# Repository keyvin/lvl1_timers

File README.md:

Maintenance interval timers for lvl1. 

Edit the defaults in micropython/lvl1_timers.py. Use Thonny to upload to micropython

reporting server a WIP

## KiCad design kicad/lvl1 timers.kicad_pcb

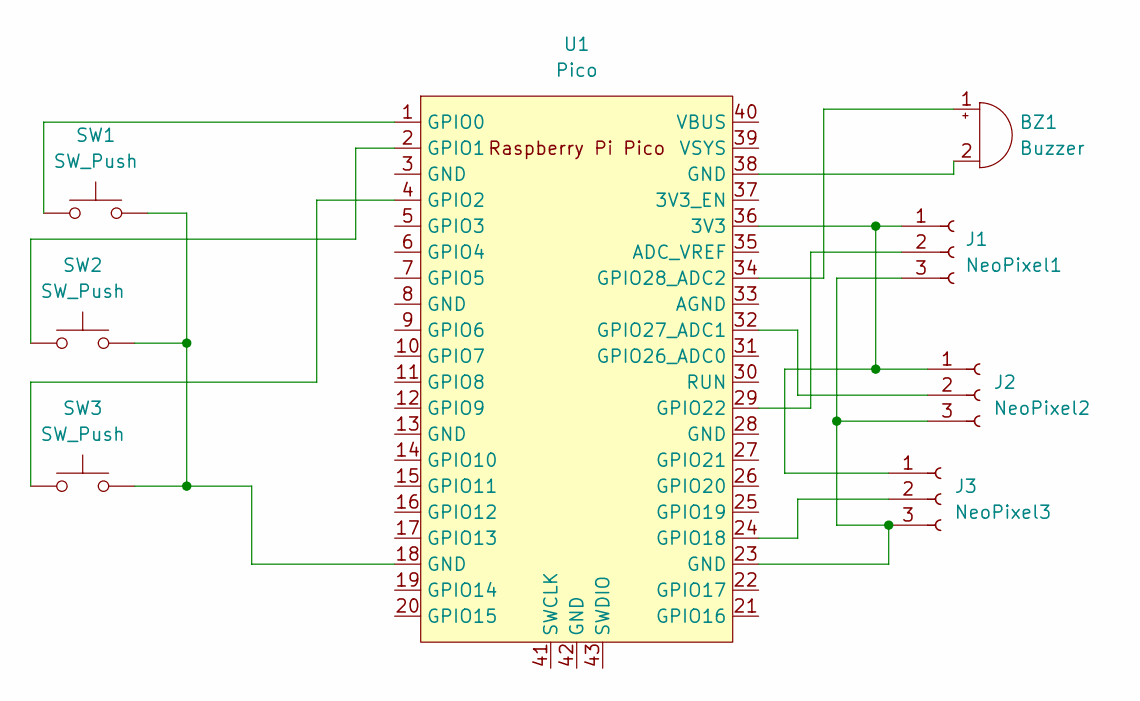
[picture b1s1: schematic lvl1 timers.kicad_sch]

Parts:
BZ1: Buzzer; Buzzer_12x9.5RM7.6
J1: NeoPixel1; PinHeader_1x03_P2.54mm_Vertical
J2: NeoPixel2; PinHeader_1x03_P2.54mm_Vertical
J3: NeoPixel3; PinHeader_1x03_P2.54mm_Vertical
SW1, SW2, SW3: SW_Push; SW_PUSH_6mm_H13mm
U1: Pico; RPi_Pico_SMD_TH

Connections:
unnamed: BZ1.1 (-), U1.34 (GPIO28_ADC2)
unnamed: BZ1.2 (+), U1.38 (GND)
unnamed: J1.1, J2.1, J3.1, U1.36 (3V3)
unnamed: J1.2, U1.29 (GPIO22)
unnamed: J2.2, U1.32 (GPIO27_ADC1)
unnamed: J3.2, U1.24 (GPIO18)
unnamed: J1.3, J2.3, J3.3, U1.23 (GND)
unnamed: SW1.1, U1.1 (GPIO0)
unnamed: SW2.1, U1.2 (GPIO1)
unnamed: SW3.1, U1.4 (GPIO2)
unnamed: SW1.2, SW2.2, SW3.2, U1.18 (GND)

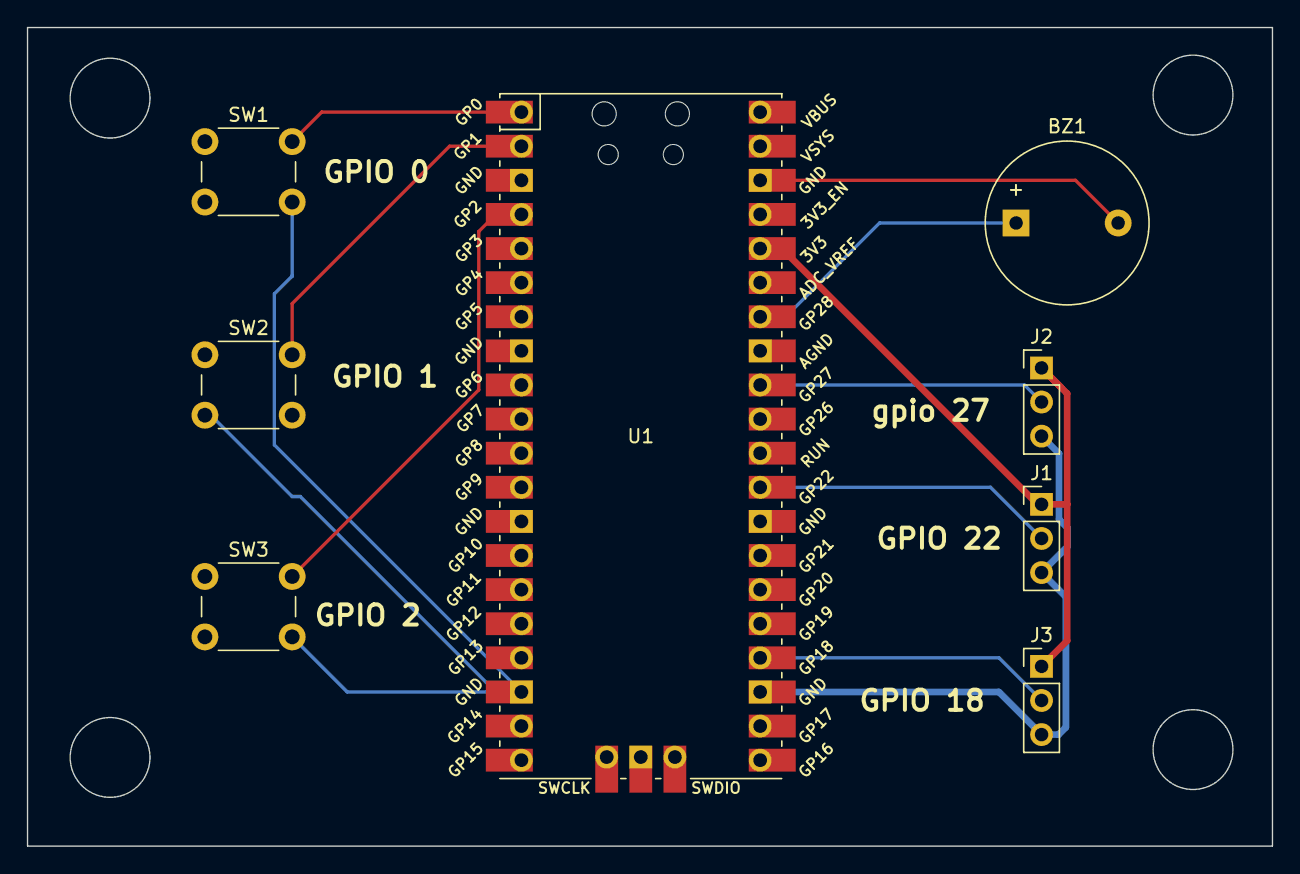
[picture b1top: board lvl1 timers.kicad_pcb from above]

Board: 2 copper layers, 92.7 x 61.0 mm, 8 parts (0 on the bottom side), 11 nets.

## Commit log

2024-01-06 Fixed bugs
2024-01-07 last for the day
2024-01-07 This better not
